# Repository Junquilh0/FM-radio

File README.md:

# FM-radio
This project is essentially a small FM radio receiver that I could build with some cheap components and some things I already had at home. I wanted to do this project because I've always loved electronics, and the way radios made it possible to hear someone that is miles away always felt like magic to me. I am building this with no microcontroller or chip that does almost everything for me because I wanted to really learn how everything works. It turns out this project was a bit more complicated than I expected, and I had to spend a lot of time learning about RLC circuits and wave filtering. Although it's not perfect, I think I designed it well enough that we can at least hear a distorted voice when it is working. It's not a perfect radio and the quality will probably be very poor, but I think I completed my goal and it's a good start.
 
### Example of inspiration:

Image from youtube video (https://www.youtube.com/watch?v=K_KGpeN28-U)
 
## How it works
 
While making this I saw a lot of different designs for similar radios. Mine is made of essentially two parts:
### The receiver
- The coil (L) and the small variable capacitor (C_osc) choose which frequency the radio "listens" to. The frequency the radio points to is around 100 MHz, and changing the capacitor or slightly adjusting the coil (it's handmade) moves it across the FM band;
- The antenna is a 75 cm wire because that's one fourth of the wavelength of a normal radio wave. It connects through a tiny 2 pF capacitor (C3) so it does not mess up the tuning;
- The transistor (Q1) makes the circuit almost oscillate, which makes it very sensitive. This type of receiver is called *super-regenerative* because it uses its positive feedback to amplify the signal;
- The second variable capacitor (C_regen) and a potentiometer (poten2) control how strongly the transistor affects the circuit;
- A small choke (inductor XRF1) and some capacitors let only the audio move on to the next stage;
- R1, C1 and C2 clean the power for the receiver;
### The amplifier (LM386)
- The sound goes through a filter (R_audio and C5) that removes the noise, then through the volume pot (poten1);
- The LM386 amplifies the audio (about 200 times) and sends it to the speaker;
- The other capacitors around the chip (C7, C8, C13, C_bypass1, C12) keep it stable and smooth the power;
## Pictures
 
Schematic:

PCB layout:

3D model:

## Wiring
 
Some parts are connected with wires because I'm still not sure about their dimensions:
 
| Part | Pad | Goes to |
|---|---|---|
| Battery | 1 | + |
| Battery | 2 | − |
| Switch | 1 | circuit (switched +9 V) |
| Switch | 2 | battery + |
| Switch | 3 | not used |
| Volume pot (10 kΩ) | 1 | audio in |
| Volume pot (10 kΩ) | 2 (middle) | LM386 pin 3 |
| Volume pot (10 kΩ) | 3 | ground |
| Regeneration pot (50 kΩ) | 1 | filtered +9 V |
| Regeneration pot (50 kΩ) | 2 (middle) | base of the transistor |
| Regeneration pot (50 kΩ) | 3 | ground |
| Speaker | 1 | amplifier output |
| Speaker | 2 | ground |
| Antenna | 1 | 75 cm wire |
 
The electrolytic capacitors have a polarity so pay attention. All the other components are soldered on the pcb as in the sketch.
 
## Bill of materials
The list below shows all the materials needed. The ones that bring more than one component are there because it was cheaper than buying one in another website (there are not many electronics stores where I live, so sorry for that).
 
| Qty | Part | Value | Where on the board | Link |
|---|---|---|---|---|
| 1 | Transistor | BF494 | Q1 | [link](https://pt.aliexpress.com/item/1005008378765100.html) |
| 1 | Amplifier chip | LM386 | U1 | [link](https://www.ptrobotics.com/audio/10381-lm386n-3-amplificador-audio-de-baixa-tensao-700mw.html) |
| 1 | Resistor | 1 kΩ | R1 | [link](https://www.ptrobotics.com/resistencias-5-250mw/45-resistencia-1k-5-250mw.html) |
| 1 | Resistor | 2.2 kΩ | R2 | [link](https://www.ptrobotics.com/resistencias-1-600mw/9094-resistencia-2k2-1-600mw.html) |
| 1 | Resistor | 10 kΩ | R_audio1 | [link](https://www.ptrobotics.com/resistencias-5-250mw/62-resistencia-10k-5-250mw.html) |
| 1 | Resistor | 10 Ω | R3 | [link](https://www.ptrobotics.com/resistencias-5-250mw/22-resistencia-10r-5-250mw.html) |
| 1 | Ceramic capacitor | 2 pF | C3 | [link](https://pt.aliexpress.com/item/1005003654568680.html) |
| 1 | Ceramic capacitor | 1.2 nF | C4 | [link](https://www.ptrobotics.com/condensador-ceramicos/12739-condensador-ceramico-12nf-50v.html) |
| 1 | Ceramic capacitor | 4.7 nF | C6 | [link](https://www.ptrobotics.com/condensador-ceramicos/2179-condensador-ceramico-47nf-50v.html) |
| 1 | Ceramic capacitor | 10 nF | C5 | [link](https://www.ptrobotics.com/condensador-ceramicos/509-condensador-ceramico-10nf-50v.html) |
| 1 | Ceramic capacitor | 47 nF | C12 | [link](https://www.ptrobotics.com/condensador-ceramicos/3508-condensador-ceramico-47nf-50v.html) |
| 1 | Ceramic capacitor | 100 nF | C2 | [link](https://pt.aliexpress.com/item/1005011819339428.html) |
| 1 | Trimmer capacitor | 2–10 pF | C_regen1 | [link](https://www.ptrobotics.com/trimmers/6906-2-10pf-variable-trimmer-capacitor.html) |
| 1 | Trimmer capacitor | 5–20 pF | C_oscilator1 | [link](https://pt.aliexpress.com/item/1005001616140065.html) |
| 3 | Electrolytic capacitor | 10 µF | C1, C7, C_bypass1 | [link](https://www.ptrobotics.com/condensador-electroliticos/518-condensador-electrolitico-10uf-25v.html) |
| 1 | Electrolytic capacitor | 1 µF | C9 | [link](https://www.ptrobotics.com/condensador-electroliticos/3398-condensador-electrolitico-1uf-16v.html) |
| 1 | Electrolytic capacitor | 100 µF | C13 | [link](https://www.ptrobotics.com/condensador-electroliticos/529-condensador-electrolitico-100uf-25v.html) |
| 1 | Electrolytic capacitor | 220 µF | C8 | [link](https://www.ptrobotics.com/condensador-electroliticos/533-condensador-electrolitico-220uf-25v.html) |
| 1 | RF choke | 10 µH | XRF1 | [link](https://www.ptrobotics.com/indutores/993-indutor-radial-10uh-15a-007r.html) |
| 1 | Potentiometer | 50 kΩ | poten2 | [link](https://www.ptrobotics.com/potenciometros-rotativos/7981-potenciometro-linear-50k-125mw-montagem-com-fio.html) |
| 1 | Potentiometer | 10 kΩ | poten1 | [link](https://www.ptrobotics.com/potenciometros-rotativos/5267-potentiometer-linear-10k-125mw.html) |
| 1 | 9 V battery clip | 9 V | BT1 | [link](https://pt.aliexpress.com/item/1005010458753879.html) |
| 1 | Switch | SPDT(one pin not used) | SW1 | No link (I have it at home) |
| 1 | Speaker | small | LS1 | No link (I have it at home) |
| 1 | 9 V battery | 9 V | BT1 | No link (I have it at home) |
| 1 | Wire | 75 cm | antenna | No link (I have it at home) |
| 1 | Enamelled copper wire | about 1 mm | coil (5 turns, wound by hand) | No link (I have it at home) |
 
## Important files
 
- `Radio_1_v2.kicad_pcb`: the PCB
- `Radio_1.kicad_sch`: the schematic
- `radio.pretty/`: footprints I made for the parts
- `images/`: pictures

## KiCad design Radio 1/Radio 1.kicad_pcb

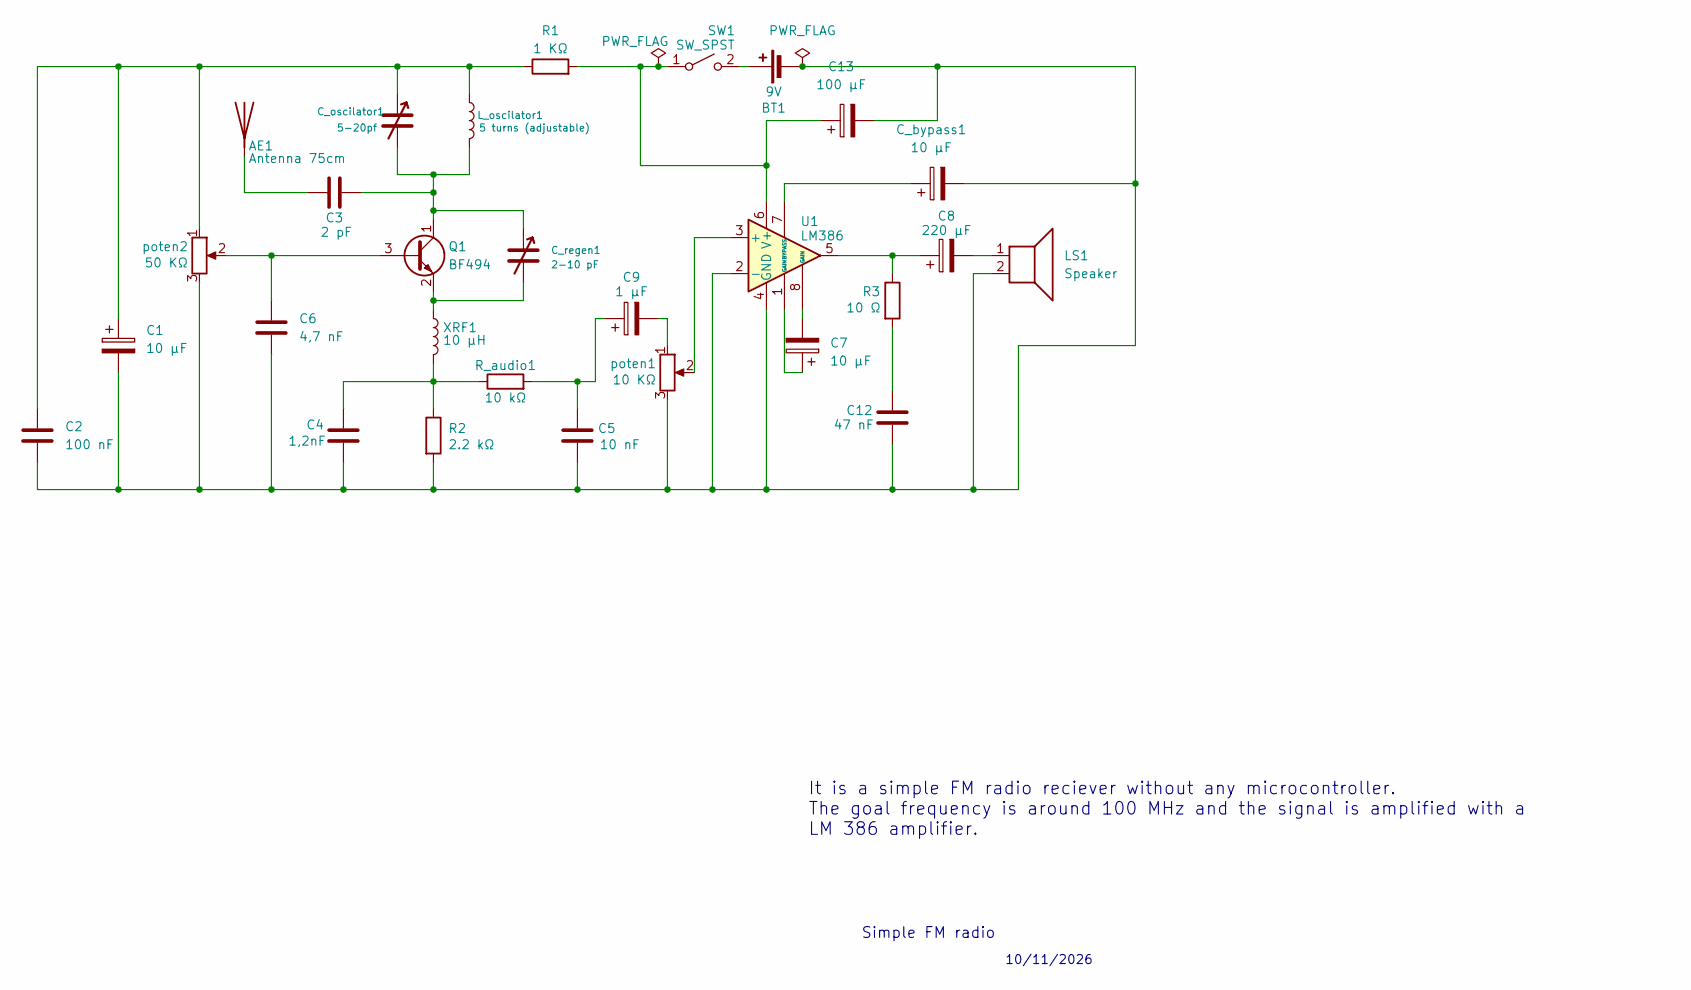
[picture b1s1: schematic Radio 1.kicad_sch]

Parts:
AE1: Antenna 75cm; Wire_1x01_P2.54mm
BT1: 9V; Wire_1x02_P2.54mm
C1, C7: 10 μF; CP_Radial_D5.0mm_P2.00mm
C2: 100 nF; C_Ceramic_Slot_P2.54-5.08mm
C3: 2 pF; C_Ceramic_Slot_P2.54-5.08mm
C4: 1,2nF; C_Ceramic_Slot_P2.54-5.08mm
C5: 10 nF; C_Ceramic_Slot_P2.54-5.08mm
C6: 4,7 nF; C_Ceramic_Slot_P2.54-5.08mm
C8: 220 μF; CP_Radial_D8.0mm_P3.50mm
C9: 1 μF; CP_Radial_D5.0mm_P2.00mm
C12: 47 nF; C_Ceramic_Slot_P2.54-5.08mm
C13: 100 μF; CP_Radial_D6.3mm_P2.50mm
C_bypass1: 10 μF; CP_Radial_D5.0mm_P2.00mm
C_oscilator1: 5-20pf; Trimmer_C_Slot_P2.5-5.08mm
C_regen1: 2-10 pF; Trimmer_C_Slot_P2.5-5.08mm
LS1: Speaker; Wire_1x02_P2.54mm
L_oscilator1: 5 turns (adjustable); L_Air_P7.62mm_Handwound
Q1: BF494; TO-92_Inline_CEB
R1: 1 KΩ; R_Axial_L6.3mm_D2.5mm_P10.16mm
R2: 2.2 kΩ; R_Axial_L6.3mm_D2.5mm_P10.16mm
R3: 10 Ω; R_Axial_L6.3mm_D2.5mm_P10.16mm
R_audio1: 10 kΩ; R_Axial_L6.3mm_D2.5mm_P10.16mm
SW1: SW_SPST; Wire_1x03_P2.54mm
U1: LM386; DIP-8_W7.62mm_LM386
XRF1: 10 μH; L_Radial_Slot_P5.0-7.5mm
poten1: 10 KΩ; Wire_1x03_P2.54mm
poten2: 50 KΩ; Wire_1x03_P2.54mm

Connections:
unnamed: AE1.1 (A_1), C3.1
unnamed: BT1.1 (+), SW1.2 (B)
unnamed: BT1.2 (-), C1.2, C2.2, C4.2, C5.2, C6.2, C12.2, C13.2, C_bypass1.2, LS1.2, R2.2, U1.2 (-), U1.4 (GND), poten1.3, poten2.3
unnamed: C1.1, C2.1, C_oscilator1.1, L_oscilator1.1, R1.1, poten2.1
unnamed: C4.1, R2.1, R_audio1.1, XRF1.2
unnamed: C5.1, C9.1, R_audio1.2
unnamed: C7.1, U1.1 (GAIN)
unnamed: C7.2, U1.8 (GAIN)
unnamed: C8.1, R3.1, U1.5
unnamed: C8.2, LS1.1
unnamed: C9.2, poten1.1
unnamed: C12.1, R3.2
unnamed: C6.1, Q1.3 (B), poten2.2
unnamed: C3.2, C_oscilator1.2, C_regen1.1, L_oscilator1.2, Q1.1 (C)
unnamed: C_regen1.2, Q1.2 (E), XRF1.1
unnamed: C13.1, R1.2, SW1.1 (A), U1.6 (V+)
unnamed: U1.3 (+), poten1.2
unnamed: C_bypass1.1, U1.7 (BYPASS)

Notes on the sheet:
10/11/2026
Simple FM radio
It is a simple FM radio reciever without any microcontroller. The goal frequency is around 100 MHz and the signal is amplified with a LM 386 amplifier.

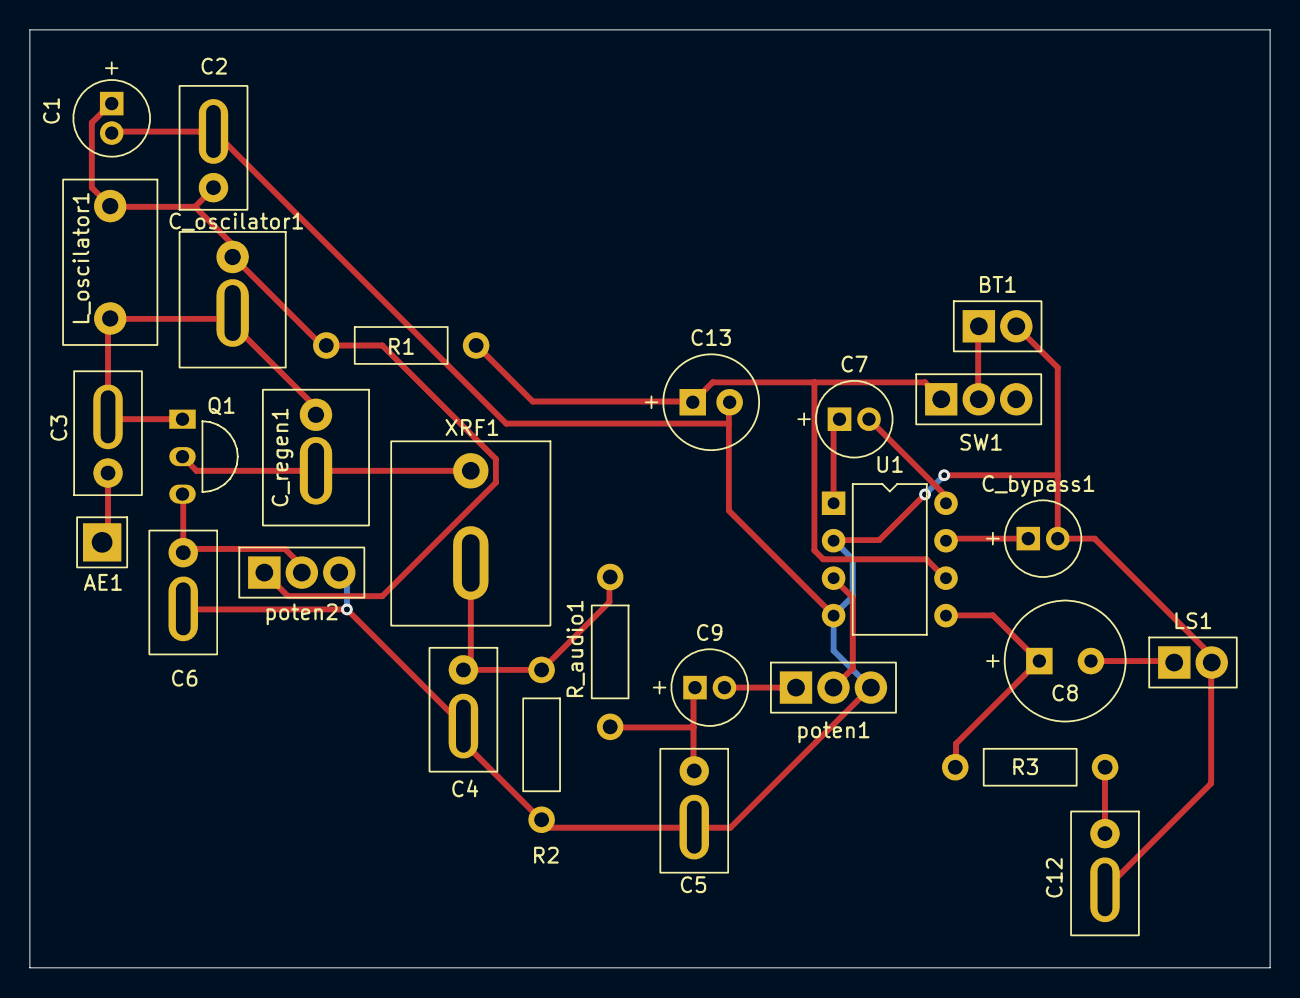
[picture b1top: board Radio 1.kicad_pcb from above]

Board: 2 copper layers, 84.1 x 63.6 mm, 28 parts (0 on the bottom side), 18 nets.
